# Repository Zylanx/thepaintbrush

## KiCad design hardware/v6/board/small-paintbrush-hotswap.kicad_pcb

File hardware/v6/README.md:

# Paintbrush Version 5

This is the fifh hardware design of the Paintbrush mini keyboard. This version adds MX switch support, a plate for MX builds and moves the MCU to a better location to accomodate thicker USB cables. The silk screens were also overhauled and can be used to guide a build without referencing these instructions.

Please see the following sections for details about this hardware version.

## Rendering

## Features

- *Reversable* PCB
  - Can be built left *OR* right handed
- Pro Micro compatible MCU foot print
- Kalih Choc v1 mechanical switches *OR* MX mechanical switches
- OLED support (optional)
- Slide switch that can be used as a power switch (optional)
- Switch plate (required for MX switch builds)
- Reset button (optional)
- Bottom plate (optional)

## Bill of Materials

Please note: the provided links are for reference. Most of these products can be found in more than one store.

For MX switch builds you'll need a switch plate, hot swap sockets and switches for your build. The below switch and socket options are for choc switch builds.

| Component | Part Information | Quantity | Purchase |
| --------- | ---------------- | -------- | -------- |
| Pro Micro MCU | Any pro micro compatible MCU that supports ZMK or QMK | 1 | N/A |
| Kalih Choc v1 Switches | Kailh low profile Switch 1350 Chocolate Keyboard Switch | 8 | [AliExpress](https://www.aliexpress.com/item/32959996455.html) |
| Kalih Hot Swap Sockets (optional if directly soldering switches) | Kailh hot swap Socket for low profile 1350 Chocolate Switches | 8 | [AliExpress](https://www.aliexpress.com/item/33023283633.html) |
| Optional OLED | Any SSD1306 I2C OLED supported by or ZMK | 1 | N/A |
| Optional Power Switch | C&K PCM12SMTR | 1 | [DigiKey](https://www.digikey.com/en/products/detail/c-k/PCM12SMTR/1640112?s=N4IgTCBcDaIAoGECyBGCBdAvkA) |
| Optional Reset button | Omron Electronics Inc-EMC Div B3U-1000P | 1 | [DigiKey](https://www.digikey.com/en/products/detail/omron-electronics-inc-emc-div/B3U-1000P/1534338) |
| Optional Bottom Plate | The bottom plate for the PCB, attach with M2 stand offs and screws | 1 | N/A |
| Optional M2 stand offs | Stand offs can be used to attach the bottom plate or add a mild angle to the obard | 2-4 | N/A |
| Optional Battery | A *lithium* battery for powering the board, we recommend 10440 or lithium polymer batteries | 1 | N/A |

## Bottom Plate

The bottom plate is wholly optional for this build. We strongly recommend including it as part of your PCB order or 3d printing it in [PA12](https://www.shapeways.com/materials/multi-jet-fusion-pa12/) or [PA12-GB](https://www.shapeways.com/materials/multi-jet-fusion-pa12gb/) at [ShapeWays](https://www.shapeways.com/) if you want a bottom plate.

The bottom plate is available as a [step file](small-paintbrush-hotswap-bottom.step) if you'd like to have it created via CNC or 3d printing independent of your PCB order.

The bottom plate can be attached using standard M2 stand offs and screws.

## Build Instructions

1. Solder hot swap sockets
    - Please note: the sockets are soldered to the **underside** of the PCB
1. Solder power switch if being used
1. Solder reset button if being used
1. Solder pro micro compatible mcu
1. Solder OLED if being used
1. Solder one pad of power header to appropriate pro micro pin if being used
1. Solder battery to power header (if being used) and ground
1. Populate switches if using hot swap sockets
1. Flash chosen firmware

## Soldering Quick References

### Left Handed Builds

### Right Handed Builds

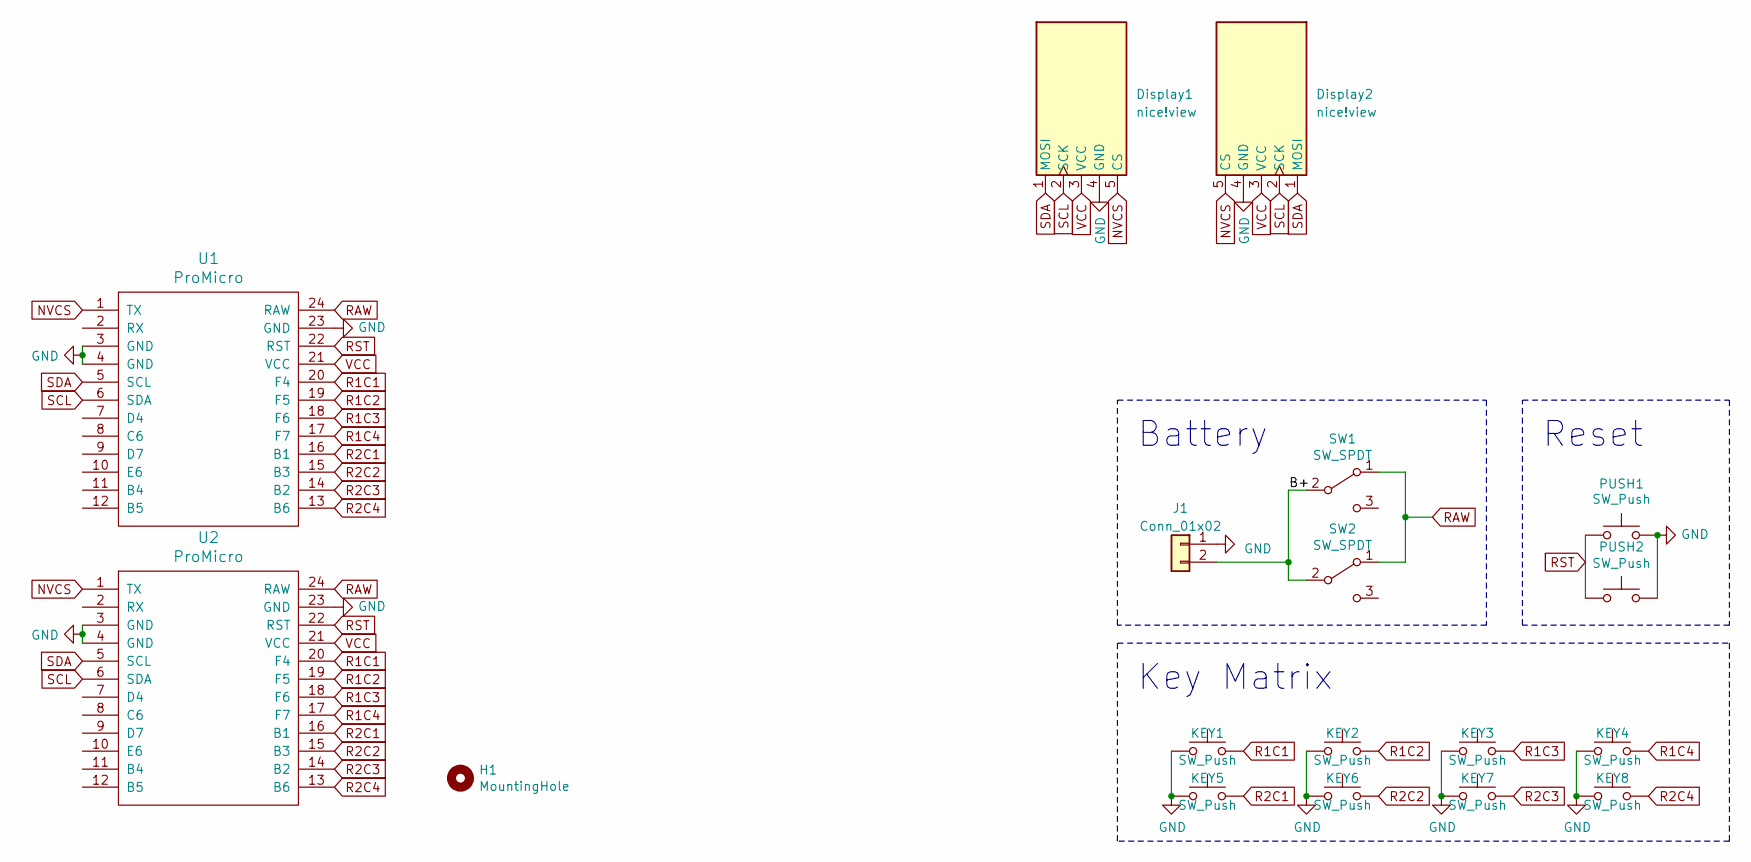
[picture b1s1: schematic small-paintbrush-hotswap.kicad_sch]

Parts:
Display1, Display2: nice!view; nice_view
H1: MountingHole; mounting-holes
J1: Conn_01x02; PinHeader_1x02_P2.54mm_Vertical
KEY1, KEY2, KEY3, KEY4, KEY5, KEY6, KEY7, KEY8: SW_Push; MX_Choc_Hotswap
PUSH1, PUSH2: SW_Push; SW_SPST_B3U-1000P
SW1, SW2: SW_SPDT; SW_SPDT_PCM12
U1, U2: ProMicro; promicro

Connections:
/B+: J1.2, SW1.2 (B), SW2.2 (B)
GND: Display1.4 (GND), Display2.4 (GND), J1.1, KEY1.1, KEY2.1, KEY3.1, KEY4.1, KEY5.1, KEY6.1, KEY7.1, KEY8.1, PUSH1.2, PUSH2.2, U1.3 (GND), U1.4 (GND), U1.23 (GND), U2.3 (GND), U2.4 (GND), U2.23 (GND)
NVCS: Display1.5 (CS), Display2.5 (CS), U1.1 (TX), U2.1 (TX)
R1C1: KEY1.2, U1.20 (F4), U2.20 (F4)
R1C2: KEY2.2, U1.19 (F5), U2.19 (F5)
R1C3: KEY3.2, U1.18 (F6), U2.18 (F6)
R1C4: KEY4.2, U1.17 (F7), U2.17 (F7)
R2C1: KEY5.2, U1.16 (B1), U2.16 (B1)
R2C2: KEY6.2, U1.15 (B3), U2.15 (B3)
R2C3: KEY7.2, U1.14 (B2), U2.14 (B2)
R2C4: KEY8.2, U1.13 (B6), U2.13 (B6)
RAW: SW1.1 (A), SW2.1 (A), U1.24 (RAW), U2.24 (RAW)
RST: PUSH1.1, PUSH2.1, U1.22 (RST), U2.22 (RST)
SCL: Display1.2 (SCK), Display2.2 (SCK), U1.6 (SDA), U2.6 (SDA)
SDA: Display1.1 (MOSI), Display2.1 (MOSI), U1.5 (SCL), U2.5 (SCL)
VCC: Display1.3 (VCC), Display2.3 (VCC), U1.21 (VCC), U2.21 (VCC)

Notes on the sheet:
Reset
Key Matrix
Battery

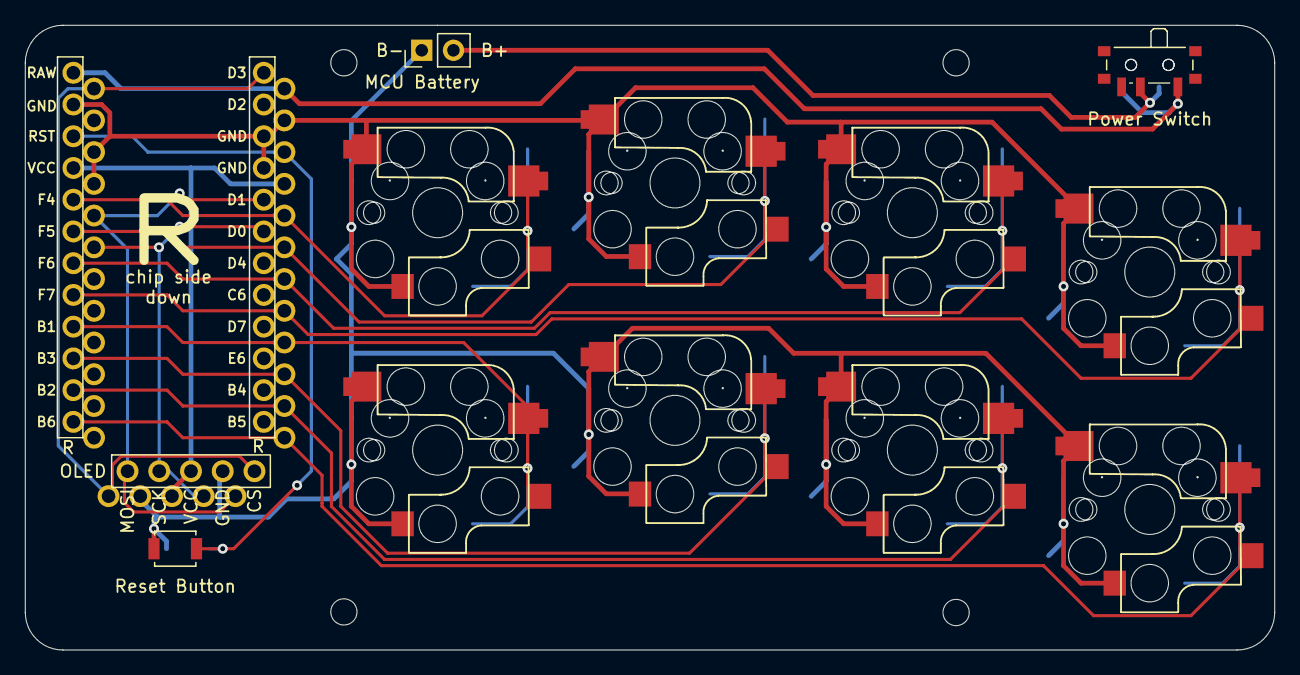
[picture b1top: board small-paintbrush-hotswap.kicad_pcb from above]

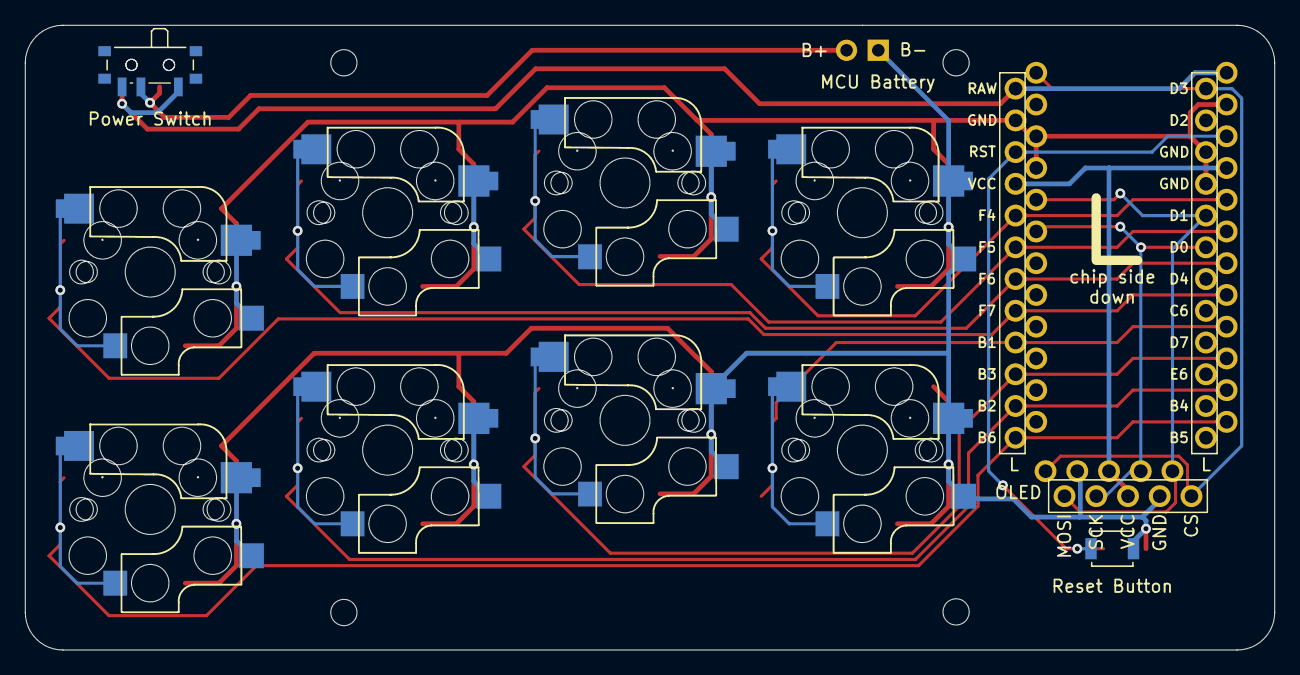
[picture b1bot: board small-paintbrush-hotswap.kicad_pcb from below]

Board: 2 copper layers, 100.0 x 50.0 mm, 18 parts (4 on the bottom side), 16 nets.

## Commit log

2023-06-16 Add my v6
    It adds a correctly routed battery connector with power switch as well as adding nice!view support hopefully
